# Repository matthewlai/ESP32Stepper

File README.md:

# ESP32Stepper

This is the PCB design and firmware for a Trinamic TMC2590-based stepper motor driver with an ESP32 microcontroller.

## Firmware Instructions

The firmware is Arduino based, using the arduino-esp32 port by Espressif.

1. Install the official Arduino IDE from [https://www.arduino.cc/en/software](https://www.arduino.cc/en/software).
2. [Install the ESP32 core](https://docs.espressif.com/projects/arduino-esp32/en/latest/installing.html) (either stable or development branch, using Board Manager).
3. Install the required libraries (see below) using Arduino library manager.
4. Clone this repository, and open ESP32Stepper/firmware/main/main.ino in the Arduino IDE.
5. In Tools, use the following settings:
    * Board: ESP32 Dev Module
    * Port: serial port for the board
    * All other settings as default (240 MHz CPU, 80 MHz flash, QIO, 4MB flash, default 4MB partition scheme, no PSRAM)

## Customisation

1. Set motor-specific parameters in config.h

## Required Libraries

1. Adafruit Neopixel 1.10.0x

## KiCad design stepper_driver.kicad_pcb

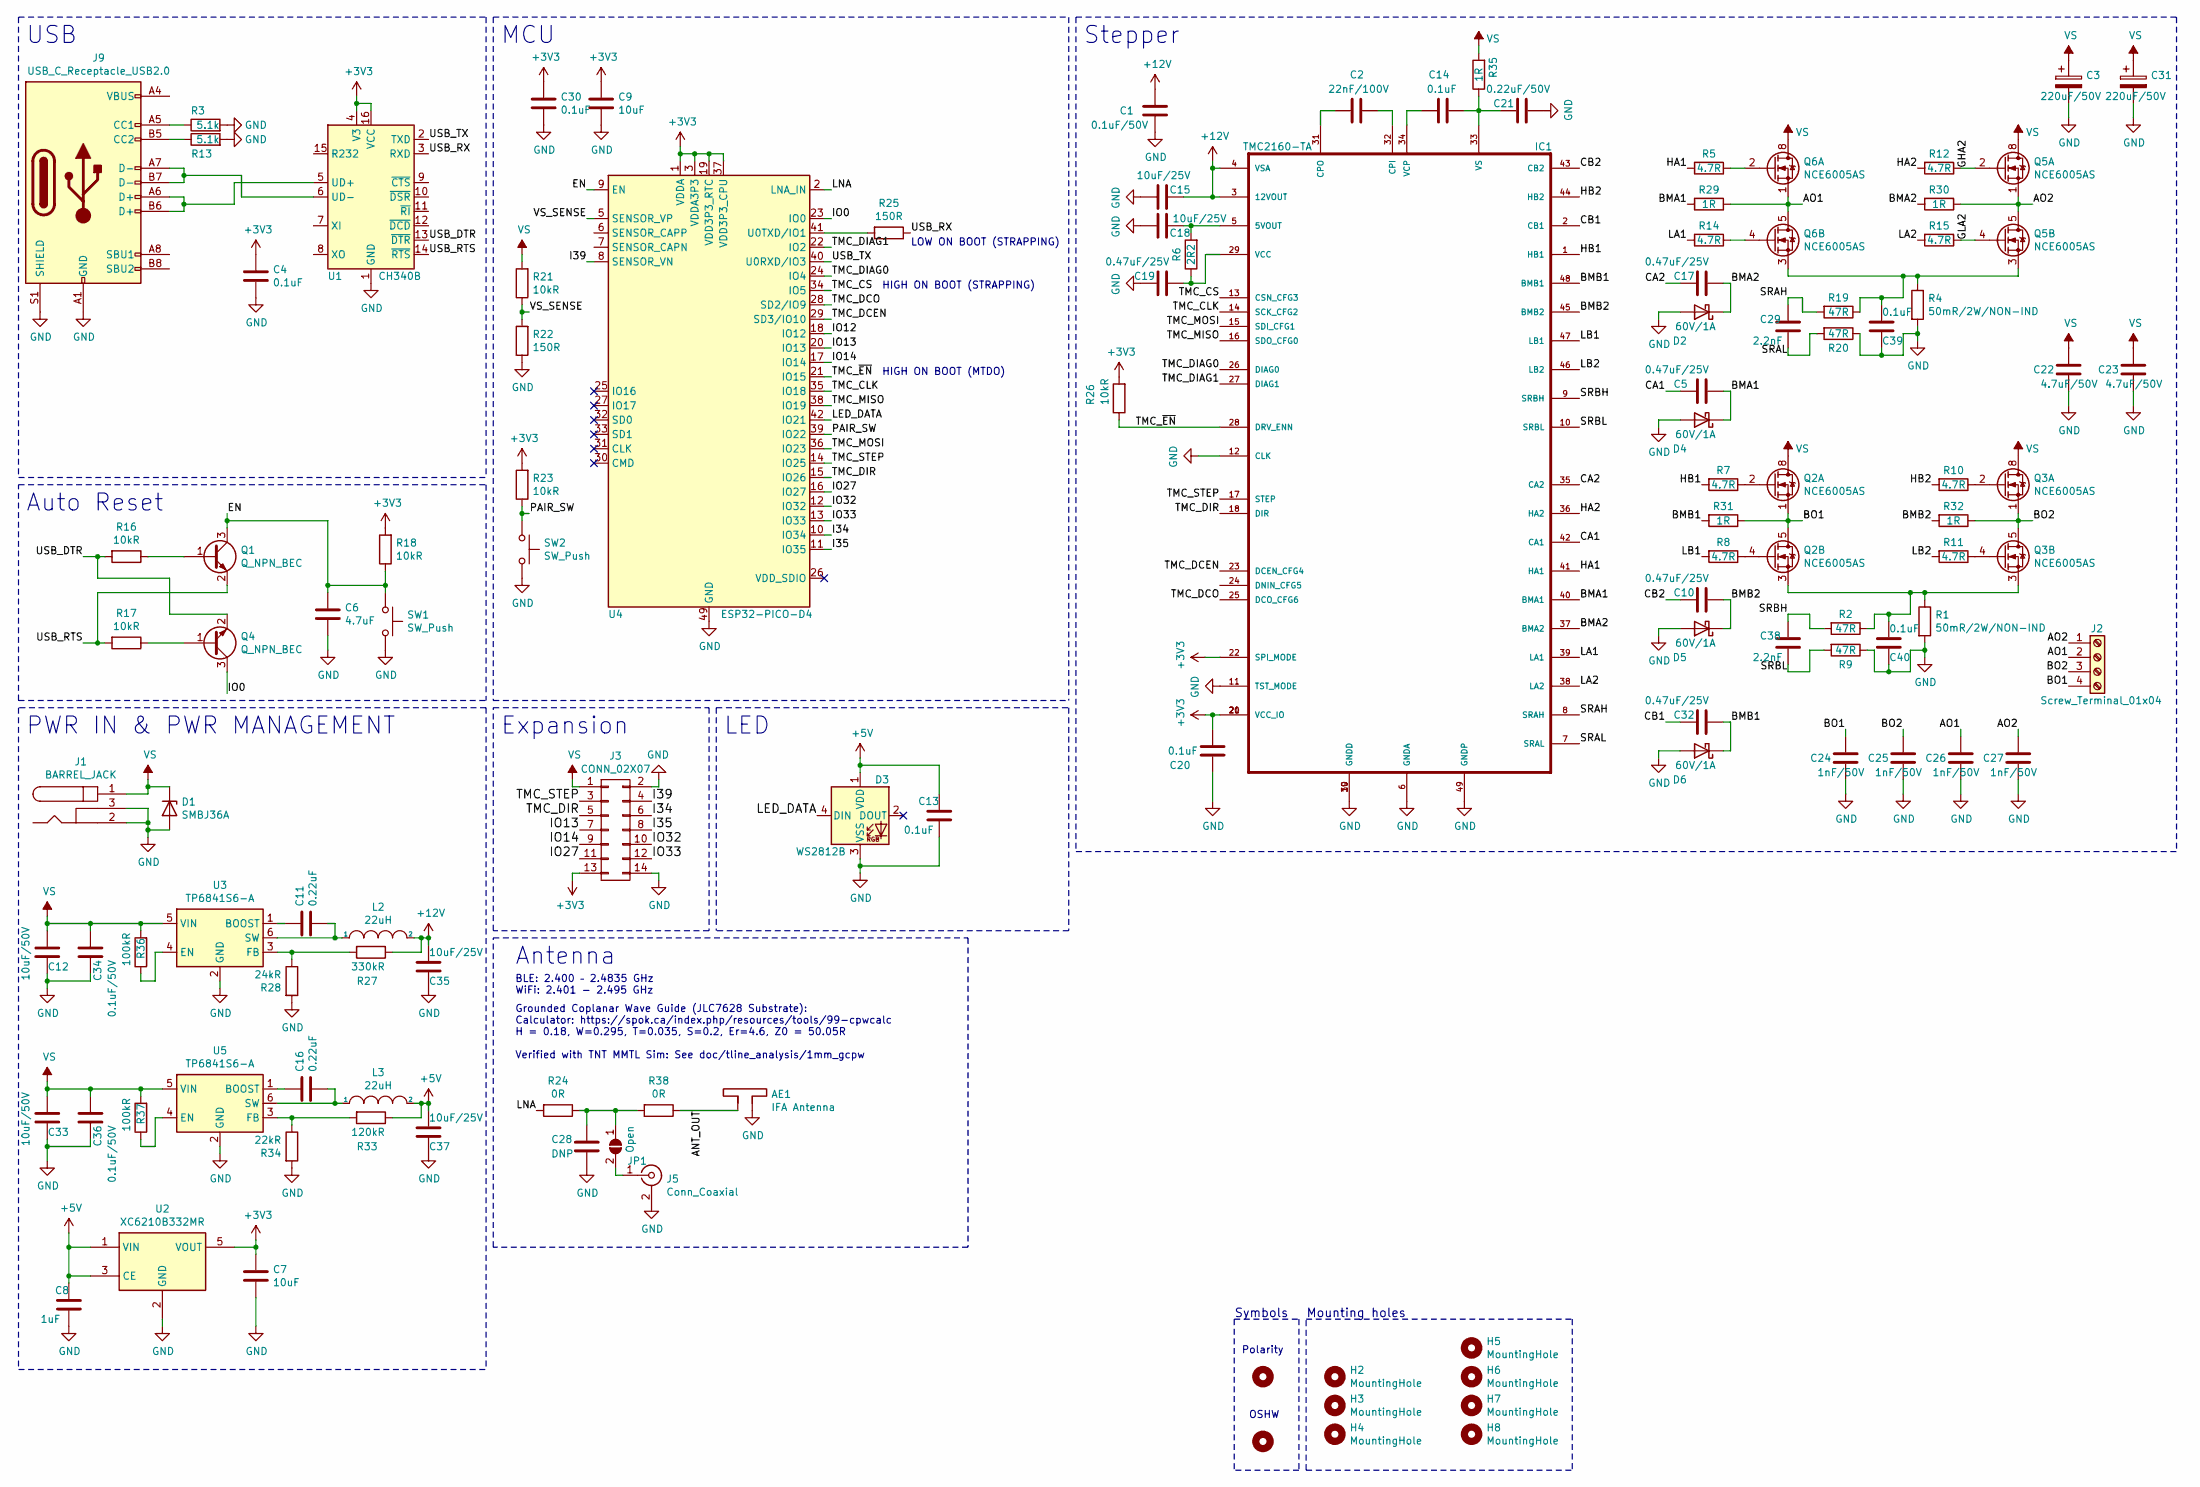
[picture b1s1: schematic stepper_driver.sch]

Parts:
AE1: IFA Antenna; TI_DN007_2.4GHz
C1: 0.1uF/50V; C_0603_1608Metric; LCSC C14663
C2: 22nF/100V; C_0603_1608Metric; LCSC C342519
C3, C31: 220uF/50V; CP_Radial_D10.0mm_P5.00mm; LCSC C88723
C4, C13, C14, C20, C30, C39, C40: 0.1uF; C_0402_1005Metric; LCSC C1525
C5, C10, C17, C19, C32: 0.47uF/25V; C_0402_1005Metric; LCSC C437527
C6: 4.7uF; C_0402_1005Metric; LCSC C23733
C7, C9: 10uF; C_0402_1005Metric; LCSC C15525
C8: 1uF; C_0402_1005Metric; LCSC C52923
C11, C16: 0.22uF; C_0402_1005Metric; LCSC C16772
C12, C33: 10uF/50V; C_1206_3216Metric; LCSC C13585
C15, C18, C35, C37: 10uF/25V; C_0603_1608Metric; LCSC C386081
C21: 0.22uF/50V; C_0805_2012Metric; LCSC C5378
C22, C23: 4.7uF/50V; C_0805_2012Metric; LCSC C162420
C24, C25, C26, C27: 1nF/50V; C_0402_1005Metric; LCSC C1523
C28: DNP; C_0603_1608Metric
C29, C38: 2.2nF; C_0402_1005Metric; LCSC C1531
C34, C36: 0.1uF/50V; C_0402_1005Metric; LCSC C307331
D1: SMBJ36A; D_SMB; LCSC C294880
D2, D4, D5, D6: 60V/1A; D_SOD-323F; LCSC C364278
D3: WS2812B; LED_WS2812B_PLCC4_5.0x5.0mm_P3.2mm; LCSC C2761795
H2, H3, H4, H5, H6, H7, H8: MountingHole; MountingHole_3.5mm
H9: MountingHole; Symbol_Barrel_Polarity
H10: MountingHole; OSHW-Logo_5.7x6mm_SilkScreen
IC1: TMC2160-TA; LQFP-48-1EP_7x7mm_P0.5mm_EP3.6x3.6mm_ThermalVias; LCSC C465948
J1: BARREL_JACK; DC-005C-25A; LCSC C223903
J2: Screw_Terminal_01x04; KF2EDGR-3.81-4P; LCSC C441184
J3: CONN_02X07; PinHeader_2x07_P2.54mm_Vertical
J5: Conn_Coaxial; U.FL_Hirose_U.FL-R-SMT-1_Vertical; LCSC C88374
J9: USB_C_Receptacle_USB2.0; USB_C_Receptacle_XKB_U262-16XN-4BVC11; LCSC C319148
JP1: Open; R_0402_1005Metric
L2, L3: 22uH; L_1210_3225Metric; LCSC C223225
Q1, Q4: Q_NPN_BEC; SOT-23; LCSC C2150
Q2, Q3, Q5, Q6: NCE6005AS; SOIC-8_3.9x4.9mm_P1.27mm; LCSC C126151
R1, R4: 50mR/2W/NON-IND; R_2512_6332Metric_Pad1.52x3.35mm_HandSolder; LCSC C160588
R2, R9, R19, R20: 47R; R_0402_1005Metric; LCSC C25118
R3, R13: 5.1k; R_0402_1005Metric; LCSC C25905
R5, R7, R8, R10, R11, R12, R14, R15: 4.7R; R_0402_1005Metric; LCSC C25121
R6: 2R2; R_0402_1005Metric; LCSC C25158
R16, R17, R18, R21, R23, R26: 10kR; R_0402_1005Metric; LCSC C25744
R22, R25: 150R; R_0402_1005Metric; LCSC C25082
R24: 0R; R_0402_1005Metric; LCSC C17168
R27: 330kR; R_0402_1005Metric; LCSC C25778
R28: 24kR; R_0402_1005Metric; LCSC C25769
R29, R30, R31, R32, R35: 1R; R_0402_1005Metric; LCSC C25086
R33: 120kR; R_0402_1005Metric; LCSC C25750
R34: 22kR; R_0402_1005Metric; LCSC C25768
R36, R37: 100kR; R_0402_1005Metric; LCSC C25741
R38: 0R; R_0603_1608Metric; LCSC C21189
SW1, SW2: SW_Push; SW_Push_1P1T_NO_5.1x5.1mm; LCSC C318887
U1: CH340B; SOIC-16_3.9x9.9mm_P1.27mm; LCSC C81010
U2: XC6210B332MR; SOT-23-5; LCSC C47719
U3, U5: TP6841S6-A; SOT-23-6; LCSC C2844924
U4: ESP32-PICO-D4; LCSC C193707

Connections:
+3V3: C4.1, C7.1, C9.1, C20.2, C30.1, IC1.20 (VCC_IO), IC1.21 (VCC_IO), IC1.22 (SPI_MODE), J3.13, R18.2, R23.2, R26.2, U1.4 (V3), U1.16 (VCC), U2.5 (VOUT), U4.1 (VDDA), U4.3 (VDDA3P3), U4.4 (VDDA3P3), U4.19 (VDD3P3_RTC), U4.37 (VDD3P3_CPU), U4.43 (VDDA), U4.46 (VDDA)
+5V: C8.1, C13.1, C37.1, D3.1 (VDD), L3.2, R33.1, U2.1 (VIN), U2.3 (CE)
+12V: C1.1, C15.2, C35.1, IC1.3 (12VOUT), IC1.4 (VSA), L2.2, R27.1
/ANT_OUT: AE1.2, R38.1
/AO1: C26.1, J2.2, Q6.1 (S1), Q6.5 (D2), Q6.6 (D2), R29.1
/AO2: C27.1, J2.1, Q5.1 (S1), Q5.5 (D2), Q5.6 (D2), R30.1
/BMA1: C5.1, D4.1 (K), IC1.40 (BMA1), R29.2
/BMA2: C17.1, D2.1 (K), IC1.37 (BMA2), R30.2
/BMB1: C32.1, D6.1 (K), IC1.48 (BMB1), R31.2
/BMB2: C10.1, D5.1 (K), IC1.45 (BMB2), R32.2
/BO1: C24.1, J2.4, Q2.1 (S1), Q2.5 (D2), Q2.6 (D2), R31.1
/BO2: C25.1, J2.3, Q3.1 (S1), Q3.5 (D2), Q3.6 (D2), R32.1
/CA1: C5.2, IC1.42 (CA1)
/CA2: C17.2, IC1.35 (CA2)
/CB1: C32.2, IC1.2 (CB1)
/CB2: C10.2, IC1.43 (CB2)
/EN: C6.1, Q1.3 (C), R18.1, SW1.1, U4.9 (EN)
/GHA2: Q5.2 (G1), R12.1
/GLA2: Q5.4 (G2), R15.1
/HA1: IC1.41 (HA1), R5.2
/HA2: IC1.36 (HA2), R12.2
/HB1: IC1.1 (HB1), R7.2
/HB2: IC1.44 (HB2), R10.2
/I34: J3.6, U4.10 (IO34)
/I35: J3.8, U4.11 (IO35)
/I39: J3.4, U4.8 (SENSOR_VN)
/IO0: Q4.3 (C), U4.23 (IO0)
/IO13: J3.7, U4.20 (IO13)
/IO14: J3.9, U4.17 (IO14)
/IO27: J3.11, U4.16 (IO27)
/IO32: J3.10, U4.12 (IO32)
/IO33: J3.12, U4.13 (IO33)
/LA1: IC1.39 (LA1), R14.2
/LA2: IC1.38 (LA2), R15.2
/LB1: IC1.47 (LB1), R8.2
/LB2: IC1.46 (LB2), R11.2
/LED_DATA: D3.4 (DIN), U4.42 (IO21)
/LNA: R24.2, U4.2 (LNA_IN)
/PAIR_SW: R23.1, SW2.1, U4.39 (IO22)
/SRAH: C29.1, IC1.8 (SRAH), R19.2
/SRAL: C29.2, IC1.7 (SRAL), R20.2
/SRBH: C38.1, IC1.9 (SRBH), R2.2
/SRBL: C38.2, IC1.10 (SRBL), R9.2
/TMC_CLK: IC1.14 (SCK_CFG2), U4.35 (IO18)
/TMC_CS: IC1.13 (CSN_CFG3), U4.34 (IO5)
/TMC_DCEN: IC1.23 (DCEN_CFG4), U4.29 (SD3/IO10)
/TMC_DCO: IC1.25 (DCO_CFG6), U4.28 (SD2/IO9)
/TMC_DIAG0: IC1.26 (DIAG0), U4.24 (IO4)
/TMC_DIAG1: IC1.27 (DIAG1), U4.22 (IO2)
/TMC_DIR: IC1.18 (DIR), J3.5, U4.15 (IO26)
/TMC_MISO: IC1.16 (SDO_CFG0), U4.38 (IO19)
/TMC_MOSI: IC1.15 (SDI_CFG1), U4.36 (IO23)
/TMC_STEP: IC1.17 (STEP), J3.3, U4.14 (IO25)
/TMC_~EN: IC1.28 (DRV_ENN), R26.1, U4.21 (IO15)
/USB_DTR: Q4.2 (E), R16.2, U1.13 (~DTR)
/USB_RTS: Q1.2 (E), R17.2, U1.14 (~RTS)
/USB_RX: R25.1, U1.3 (RXD)
/USB_TX: U1.2 (TXD), U4.40 (U0RXD/IO3)
/VS_SENSE: R21.1, R22.2, U4.5 (SENSOR_VP)
GND: AE1.1, C1.2, C3.2, C4.2, C6.2, C7.2, C8.2, C9.2, C12.2, C13.2, C15.1, C18.1, C19.2, C20.1, C21.2, C22.2, C23.2, C24.2, C25.2, C26.2, C27.2, C28.2, C30.2, C31.2, C33.2, C34.1, C35.2, C36.1, C37.2, C39.2, C40.2, D1.2 (A), D2.2 (A), D3.3 (VSS), D4.2 (A), D5.2 (A), D6.2 (A), IC1.6 (GNDA), IC1.11 (TST_MODE), IC1.12 (CLK), IC1.19 (GNDD), IC1.30 (GNDD), IC1.49 (GNDP), J1.2, J1.3, J3.2, J3.14, J5.2 (Ext), J9.A1 (GND), J9.A12 (GND), J9.B1 (GND), J9.B12 (GND), J9.S1 (SHIELD), R1.2, R3.2, R4.2, R9.1, R13.2, R20.1, R22.1, R28.2, R34.2, SW1.2, SW2.2, U1.1 (GND), U2.2 (GND), U3.2 (GND), U4.49 (GND), U5.2 (GND)
unnamed: C2.1, IC1.32 (CPI)
unnamed: C2.2, IC1.31 (CPO)
unnamed: C11.1, U3.1 (BOOST)
unnamed: C11.2, L2.1, U3.6 (SW)
unnamed: C14.1, IC1.34 (VCP)
unnamed: C14.2, C21.1, IC1.33 (VS), R35.1
unnamed: C16.1, U5.1 (BOOST)
unnamed: C16.2, L3.1, U5.6 (SW)
unnamed: C18.2, IC1.5 (5VOUT), R6.2
unnamed: C19.1, IC1.29 (VCC), R6.1
unnamed: C28.1, JP1.1 (A), R24.1, R38.2
unnamed: C39.1, Q5.3 (S2), Q6.3 (S2), R4.1, R19.1
unnamed: C40.1, Q2.3 (S2), Q3.3 (S2), R1.1, R2.1
unnamed: J5.1 (In), JP1.2 (B)
unnamed: J9.A4 (VBUS), J9.A9 (VBUS), J9.B4 (VBUS), J9.B9 (VBUS)
unnamed: J9.A5 (CC1), R3.1
unnamed: J9.A6 (D+), J9.B6 (D+), U1.5 (UD+)
unnamed: J9.A7 (D-), J9.B7 (D-), U1.6 (UD-)
unnamed: J9.B5 (CC2), R13.1
unnamed: Q1.1 (B), R16.1
unnamed: Q2.2 (G1), R7.1
unnamed: Q2.4 (G2), R8.1
unnamed: Q3.2 (G1), R10.1
unnamed: Q3.4 (G2), R11.1
unnamed: Q4.1 (B), R17.1
unnamed: Q6.2 (G1), R5.1
unnamed: Q6.4 (G2), R14.1
unnamed: R25.2, U4.41 (U0TXD/IO1)
unnamed: R27.2, R28.1, U3.3 (FB)
unnamed: R33.2, R34.1, U5.3 (FB)
unnamed: R36.1, U3.4 (EN)
unnamed: R37.1, U5.4 (EN)
VS: C3.1, C12.1, C22.1, C23.1, C31.1, C33.1, C34.2, C36.2, D1.1 (K), J1.1, J3.1, Q2.7 (D1), Q2.8 (D1), Q3.7 (D1), Q3.8 (D1), Q5.7 (D1), Q5.8 (D1), Q6.7 (D1), Q6.8 (D1), R21.2, R35.2, R36.2, R37.2, U3.5 (VIN), U5.5 (VIN)

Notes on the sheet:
Mounting holes
USB
Auto Reset
MCU
LED
PWR IN & PWR MANAGEMENT
Expansion
Stepper
Antenna
BLE: 2.400 – 2.4835 GHz WiFi: 2.401 - 2.495 GHz
Grounded Coplanar Wave Guide (JLC7628 Substrate): Calculator: https://spok.ca/index.php/resources/tools/99-cpwcalc H = 0.18, W=0.295, T=0.035, S=0.2, Er=4.6, Z0 = 50.05R Verified with TNT MMTL Sim: See doc/tline_analysis/1mm_gcpw
Symbols
Polarity
OSHW
HIGH ON BOOT (STRAPPING)
HIGH ON BOOT (MTDO)
LOW ON BOOT (STRAPPING)

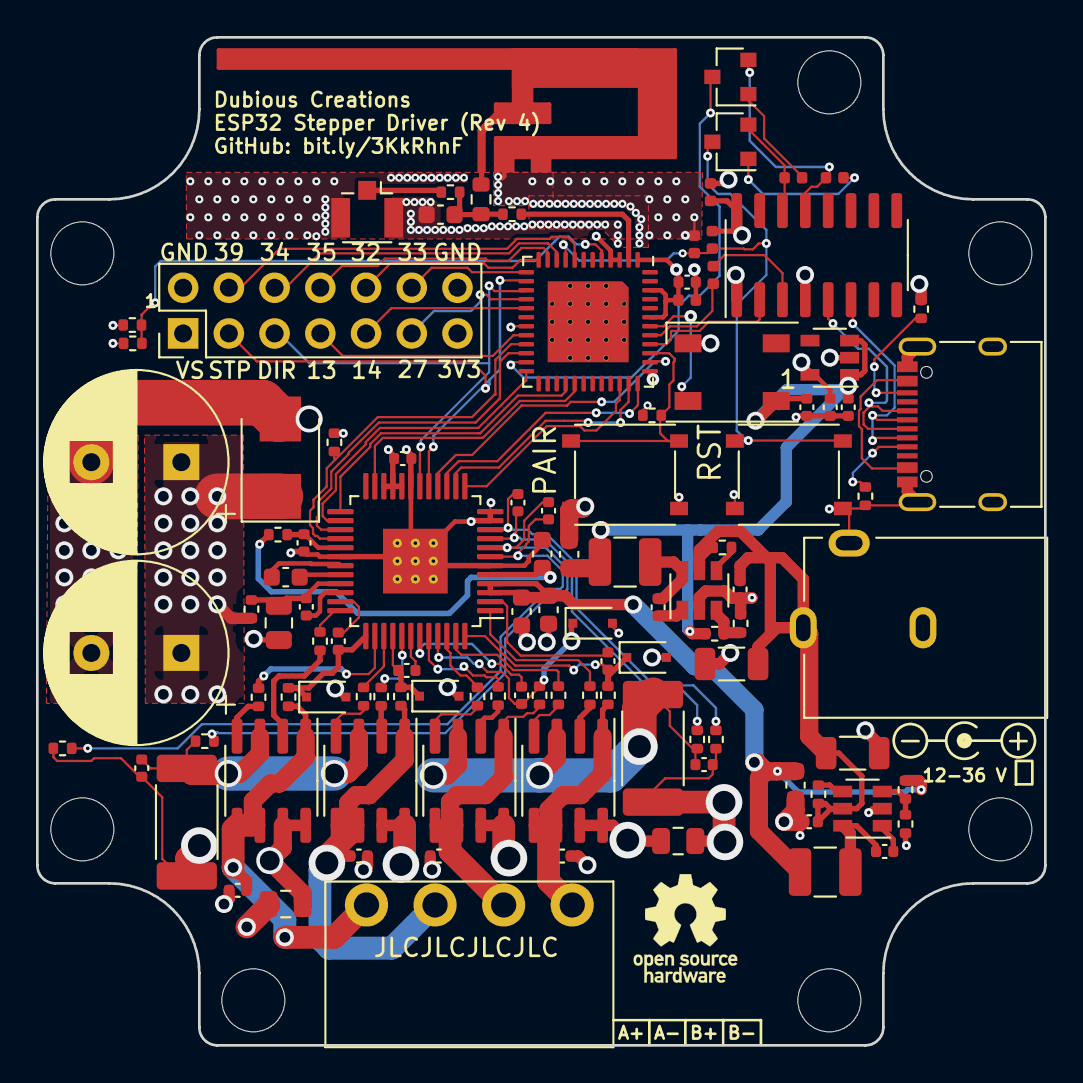
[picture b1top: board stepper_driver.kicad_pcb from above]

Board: 4 copper layers, 56.0 x 56.0 mm, 116 parts (0 on the bottom side), 93 nets.

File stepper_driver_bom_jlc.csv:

"Comment","Designator","Footprint","LCSC Part #"
"0.1uF/50V","C1,C21","C_0603_1608Metric","C14663"
"22nF/100V","C2","C_0603_1608Metric","C342519"
"470uF/50V","C3","CP_Radial_D10.0mm_P5.00mm","C106526"
"0.1uF","C4,C13,C20,C14","C_0402_1005Metric","C1525"
"4.7uF","C6","C_0402_1005Metric","C23733"
"1uF","C8","C_0402_1005Metric","C52923"
"10uF","C9,C7","C_0402_1005Metric","C15525"
"1uF/50V","C11","C_0603_1608Metric","C15849"
"330uF/16V","C12","CP_Elec_8x10.5","C110162"
"10uF/25V","C15,C18","C_0603_1608Metric","C96446"
"0.47uF/25V","C19,C5,C10,C16,C17","C_0402_1005Metric","C437527"
"4.7uF/50V","C22,C23","C_0805_2012Metric","C162420"
"1nF/50V","C27,C26,C25,C24","C_0402_1005Metric","C1523"
"D_Schottky","D2,D4,D1","D_SOD-123","C8598"
"WS2812B","D3","LED_WS2812B_PLCC4_5.0x5.0mm_P3.2mm","C2761795"
"TMC2160-TA","IC1","LQFP-48-1EP_7x7mm_P0.5mm_EP3.6x3.6mm_ThermalVias","C465948"
"BARREL_JACK","J1","DC-005C-25A","C223903"
"Screw_Terminal_01x04","J2","KF2EDGR-3.81-4P","C441184"
"USB_C_Receptacle_USB2.0","J9","USB_C_Receptacle_HRO_TYPE-C-31-M-12","C165948"
"68uH","L2","L_Taiyo-Yuden_NR-60xx","C83460"
"Q_NPN_BEC","Q1,Q4","SOT-23","C2150"
"Si4946BEY","Q2,Q3,Q6,Q5","SOIC-8_3.9x4.9mm_P1.27mm","C83862"
"50mR/2W/NON-IND","R1,R4","R_2512_6332Metric_Pad1.52x3.35mm_HandSolder","C160588"
"47R","R2,R9,R19,R20","R_0402_1005Metric","C25118"
"5.1k","R3,R13","R_0402_1005Metric","C25905"
"2R2","R6","R_0402_1005Metric","C25158"
"10R","R7,R8,R11,R10,R5,R14,R15,R12","R_0402_1005Metric","C25077"
"10kR","R16,R17,R18,R21,R23","R_0402_1005Metric","C25744"
"470R","R25,R22","R_0402_1005Metric","C25117"
"SW_Push","SW1,SW2","SW_Push_1P1T_NO_5.1x5.1mm","C318887"
"CH340B","U1","SOIC-16_3.9x9.9mm_P1.27mm","C81010"
"XC6210B332MR","U2","SOT-23-5","C47719"
"XL1509-5.0","U3","SOIC-8_3.9x4.9mm_P1.27mm","C61063"
"ESP32-WROOM-32D","U4","ESP32-WROOM-32","C473012"
"SN74LV1T34DBV","U6","SOT-23-5","C100024"

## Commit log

2021-11-20 Added PCB v1
2021-11-20 Implemented motion controller
2021-11-24 Simplified control loop and implemented StallGuard thresholds for each direction
2021-11-28 Improved control loop scheduling, and added jerk limiting (s-curve trajectory)
2021-11-28 Simplified homing procedure
2021-11-29 Changed motion planner to use rev/s units internally, and added a position based control interface
2021-12-06 Implemented direction switching flag, better homing, and tuned max speed/acceleration/jerk
2021-12-20 Hardware design v2 with TMC2160 driver and NEMA 23 form factor for mounting
2021-12-22 Added initial BLE controller and firmware support
2021-12-23 Added option to control verbose trajctory debug printing
2021-12-23 Reverted control loop to 200Hz
2021-12-23 Changed BLE server to only allow one connection at a time
2021-12-23 Completed remote control UI
2021-12-23 Added fix for potential delay time overflow
2021-12-23 Added windows icon
2021-12-24 Refactored TMC driver to support alternative IC, and improved low speed / idling
2021-12-29 Refactored homing controller out into own class, and started TMC2160 driver
2021-12-29 Removed stray manufacturing files
2021-12-30 Removed some more temp files
2021-12-30 Minor board updates
2021-12-30 Made trajectory calculations more robust
2021-12-30 Finished basic impl of TMC2160 driver
2022-01-02 Updated schematics and PCB doc
2022-01-02 Added more fet driver tuning for TMC2160
2022-01-02 Added scope shot for troubleshooting
2022-01-14 Unified units
2022-01-14 Added function to disable tmc2590
2022-01-14 Optimised 2160 gate driver config
2022-01-14 Added firmware crash handler
2022-01-14 Updated hardware to rev 3
2022-01-14 More config cleanup
2022-01-14 Implemented latching stall detection for TMC2160
2022-01-15 Improved board revision handling
2022-01-15 Rev3 PCB tweaks
2022-01-15 Board documentation re-org
2022-01-15 Added PNG schematics
2022-01-15 Cosmetics update
2022-01-18 Finalised rev3 files
2022-01-18 Minor PCB cleanup and updated tline analysis
2022-02-02 Added firmware support for rev3 board
2022-02-02 Added spacer for NEMA 23 stepper + rev 3 board
